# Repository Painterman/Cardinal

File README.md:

# Cardinal

 Introducing: Cardinal, a split, fully wireless, low profile with choc spacing and hotswap sockets with optional encoders, screens and 5 position switches.

 As this update this should be in a working state and mostly finished, you can find the Kicad project Gerbers ready to order, and the case files in /Case
 
# Why?

For a while now I have been using a ferris sweep on and off and wanted to go back to more keys and features. 
Looking at other keyboard projects i found about the Panasonic EVQWGD encoders and the 5 position switches like SKRHA line from alps and wanted to make a keyboard with both of these, options for displays and other features that I might like.

Fast-forward and here we are, my first keyboard design taking clues from multiple other community designs.

# Features

    -Fully wireless, designed around Nice!Nano or other controllers with the same pinout/wireless capability due to the lack of trss jack.
    -Reversible pcb.
    -2 encoders support per side, or 1 encoder and 1 5 position switch.
    -Choc spacing and hotswap sockets.
    -Oled display or Nice!View support.

 Things i might end up doing:
 
    - More versions: support for different encoders and for less keys.
    - Maybe a reduced choc spacing board.
    - Non hotswap version.
    - investigate into wireless charging

# BOM

Use this as a reference, you can find a more detailed build guide on the wiki.

| Part      | Quantity | Notes| 
| :-------------- | :---: | :------ |
| PCB | 2 | Use your preferred pcb manufacturing service, mine came from pcbgogo (not affiliated), the size of the pcbs is 135x100, so its a bit more expensive than the sub 100x100 |
| Pro Micro footprint microcontroller | 2 | Designed with Nice!Nano Bluetooth in mind, I’m using ProMicro NRF52840 |
| Choc key switches | 42 or less | You have the option to breakaway the extra pinkie column, or even just use less thumb keys |
| Choc hotswap sockets | Same as switches | 1 per key|
| 1N4148WS SOD123 diodes  | 48 or less | 1 per key, 2 per half for encoders and 2 for 5 way switch | 
| EVQWGD001 rotary encoders | 4 or less | I’m using only 2, but the board supports up to 4(2 per side)|
| 5-way switches SKRHA family   | 2 | SKRHADE010 are rated for more uses, I’m using SKRHABE010, rated for 1/5 the cycles and less expensive, here is the dataset : [SKRHA](https://www.mouser.es/datasheet/2/15/SKRH-1370966.pdf)|
| On/Off switch MSK-12C02 | 1 | Off to the right, on to the left, same on both halves |
| Lipo battery’s | 2 | You can use any you want, i like the 301230 size so it fits under the Pro Micro, but a bigger battery and a case it’s also a great option |
| Battery connectors | 2 | (optional) You can use any connector you like/have as long as the pitch its 1,5 mm, I’m using JST ZH|
| Reset switch | 2 | (optional) B3U-1000P|
| Keycaps | Same as switches | I like chosfox CFX and MBK, using CFX atm |
| 5-way switch keycap | 2 | I’m using ones that I don’t like until I design something better |
| Case | 2 | 3d printed case |

Most parts can be found on aliexpress easily, and I have seem a few offers to manufacture pcbs from vendors there, I have not tried any. My pcbs were ordered from [PCBgogo](https://www.pcbgogo.com/) and so far I’m happy with the cuality of the service and pcbs, im not affiliated with then but for now I can recommend then. Other popular option for manufacturing on the cheap is [JLCPCB](https://jlcpcb.com/) and can also recommend then, probably a better option overall due to shipping and EU import duties, prices were similar.

In terms of tenting options, the pcbs have 2 holes to support [Tenting Puck](https://splitkb.com/products/tenting-puck), i have not tested then as i don´t have any, but should fit. You could go with a case and cheap magnetic ring.

# Case

I have designed a simple case to use with the keyboard and to have a flat bottom so I can stick some kind of tenting option, I now use small kickstands for laptops.

The case design is really basic and also used it to try different cad programs so I can break free from fusion360 or other alternatives that are mostly online. Unfortunately, I will say that fusion and on shape are still the best options by a long shot for designing functional parts and Freecad/Ondsel are way too restrictive/hard to use. Even so I did end up using Ondsel to make the designs and on the /Case folder you can find stls for a 42 and 36 key configurations as well as svgs with the board outline, dxf to import into cad programs and my full Freecad project in case you wish to edit or modify then.

For printing the case, use any matterial you like and least 2 outer walls, so they end up solid, should print fine in all printers.

# Firmware

As this is a fully wireless build and intended to be used with [nice!nanos](), this board is intended to be used with [zmk]().
You can check my [main configuration](https://github.com/Painterman/zmk-config-cardinal) of the keyboard and in case you want to build your own firmware you could clone my main or use the [zmk module](https://github.com/Painterman/zmk-keyboard-cardinal) provided.
Both cases are [zmk studio](https://zmk.dev/docs/features/studio) and [keymap editor](https://github.com/nickcoutsos/keymap-editor) ready, for ease of use.

# Bling

Some photos, you can find more in the Pictures folder

# Inspirations and acknowledgments

First thanks to that weird friend with his weird keyboards

Heavy inspiration from Sweep https://github.com/davidphilipbarr/Sweep taking the overall shape and column stagger from it, as the reversible pcb design.

Extra pinkie column like corne https://github.com/foostan/crkbd as well as hotswap.

Inspiration from Hillside https://github.com/mmccoyd/hillside as its close to what I wanted, but also an encouragement to go further.

Encoder from Rollow  https://www.barbellboards.com/product/rollow as I fell in love with it.

5 position switches from Fulcrum https://github.com/dschil138/Fulcrum but with more keys.

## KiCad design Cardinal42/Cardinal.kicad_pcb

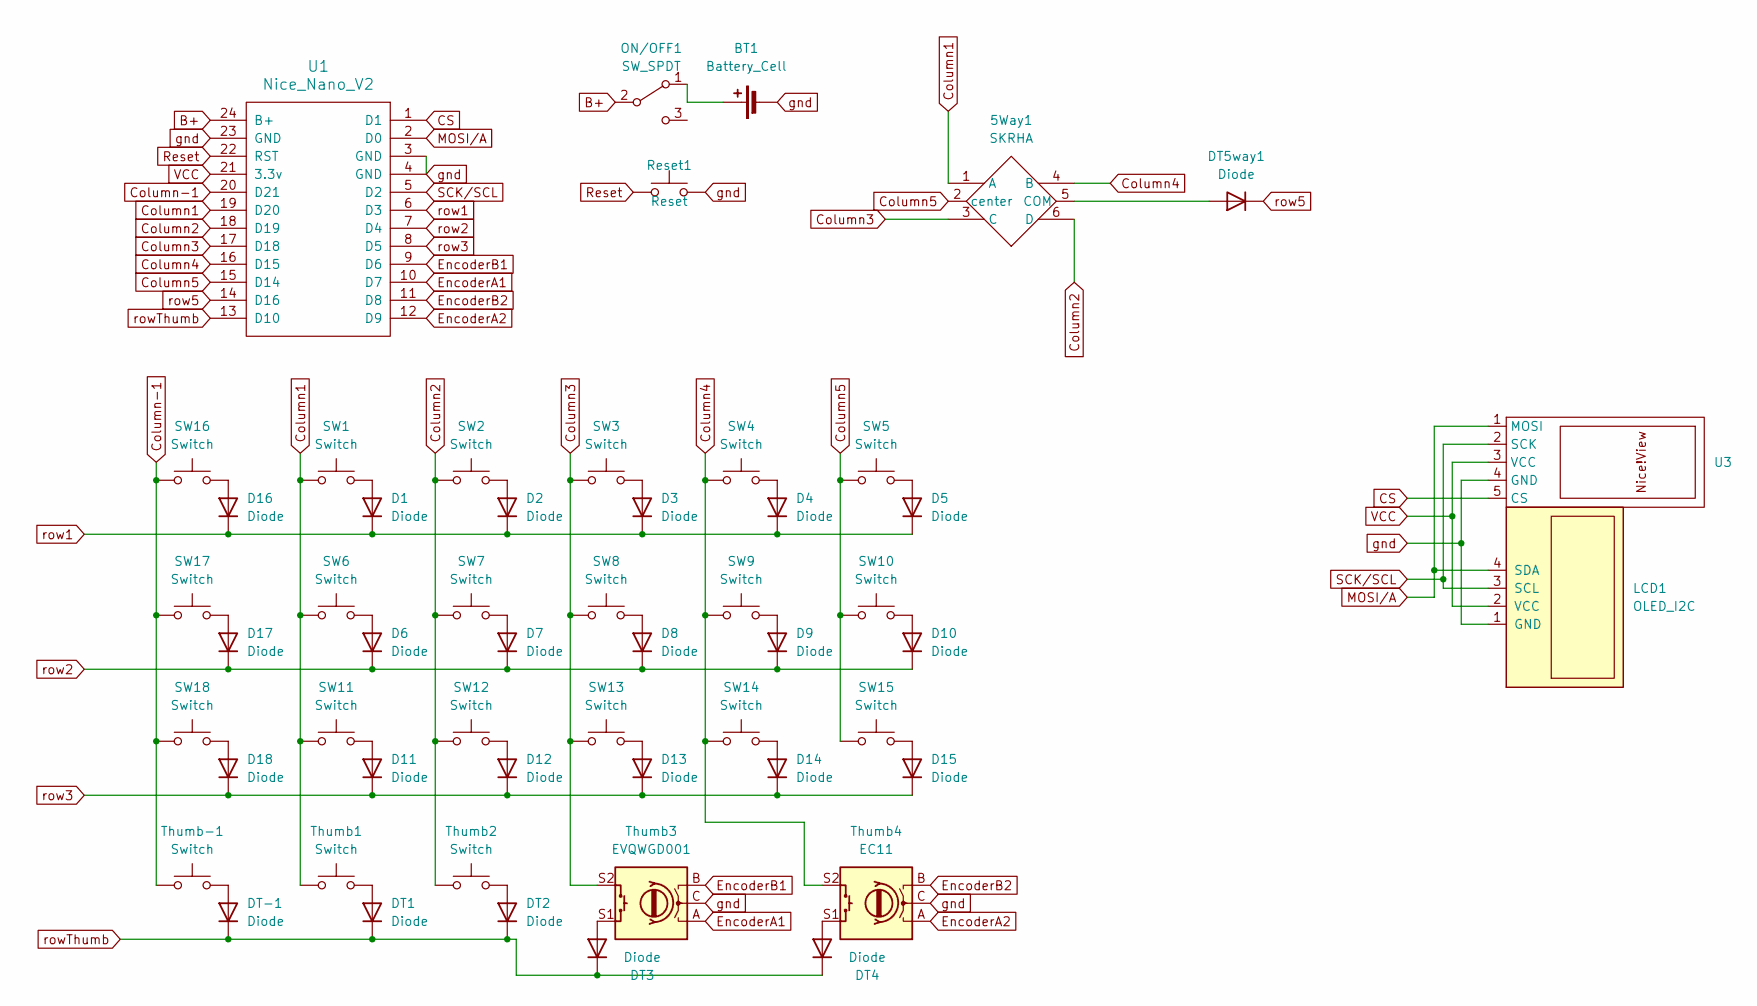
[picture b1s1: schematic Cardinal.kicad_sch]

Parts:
5Way1: SKRHA; SKRHA-boss_mod_doble
BT1: Battery_Cell; JST_ZH_2PIN_1.5MM
D1, D2, D3, D4, D5, D6, D7, D8, D9, D10, D11, D12, D13, D14, D15, D16, D17, D18: Diode; Diode_SOD-123_mod
DT1, DT2, DT3, DT4, DT5way1: Diode; Diode_SOD-123_mod
DT-1: Diode; Diode_SOD-123_mod
LCD1: OLED_I2C; OLED_I2C_128x32+NiceView
ON/OFF1: SW_SPDT; switch-MSK-12C02-smd
Reset1: Reset; SW_SPST_B3U-1000P_mod
SW1, SW2, SW3, SW4, SW5, SW6, SW7, SW8, SW9, SW10, SW11, SW12, SW13, SW14, SW15, SW16, SW17, SW18: Switch; Hotswap_Choc_V1_1.00u_mod
Thumb1, Thumb2: Switch; Hotswap_Choc_V1_1.00u_mod
Thumb3: EVQWGD001; RollerEncoder_Panasonic_EVQWGD001_mod
Thumb4: EC11; RollerEncoder_Panasonic_EVQWGD001_mod
Thumb-1: Switch; Hotswap_Choc_V1_1.00u_mod
U1: Nice_Nano_V2; ProMicro_jumpers
U3: (no value)

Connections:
B+: ON/OFF1.2 (B), U1.24 (B+)
CS: U1.1 (D1), U3.5 (CS)
Column1: 5Way1.1 (A), SW1.1, SW6.1, SW11.1, Thumb1.1, U1.19 (D20); also elsewhere on the board
Column2: 5Way1.6 (D), SW2.1, SW7.1, SW12.1, Thumb2.1, U1.18 (D19); also elsewhere on the board
Column3: 5Way1.3 (C), SW3.1, SW8.1, SW13.1, Thumb3.S2, U1.17 (D18); also elsewhere on the board
Column4: 5Way1.4 (B), SW4.1, SW9.1, SW14.1, Thumb4.S2, U1.16 (D15); also elsewhere on the board
Column5: 5Way1.2 (center), SW5.1, SW10.1, SW15.1, U1.15 (D14); also elsewhere on the board
Column-1: SW16.1, SW17.1, SW18.1, Thumb-1.1, U1.20 (D21)
EncoderA1: Thumb3.A, U1.10 (D7)
EncoderA2: Thumb4.A, U1.12 (D9)
EncoderB1: Thumb3.B, U1.9 (D6)
EncoderB2: Thumb4.B, U1.11 (D8)
MOSI/A: LCD1.4 (SDA), U1.2 (D0), U3.1 (MOSI)
unnamed 13: 5Way1.5 (COM), DT5way1.2 (A); also elsewhere on the board
unnamed 14: BT1.1 (+), ON/OFF1.1 (A); also elsewhere on the board
unnamed: D1.2 (A), SW1.2
unnamed: D2.2 (A), SW2.2
unnamed: D3.2 (A), SW3.2
unnamed: D4.2 (A), SW4.2
unnamed: D5.2 (A), SW5.2
unnamed: D6.2 (A), SW6.2
unnamed: D7.2 (A), SW7.2
unnamed: D8.2 (A), SW8.2
unnamed: D9.2 (A), SW9.2
unnamed: D10.2 (A), SW10.2
unnamed: D11.2 (A), SW11.2
unnamed: D12.2 (A), SW12.2
unnamed: D13.2 (A), SW13.2
unnamed: D14.2 (A), SW14.2
unnamed: D15.2 (A), SW15.2
unnamed: D16.2 (A), SW16.2
unnamed: D17.2 (A), SW17.2
unnamed: D18.2 (A), SW18.2
unnamed: DT1.2 (A), Thumb1.2
unnamed: DT2.2 (A), Thumb2.2
unnamed: DT3.2 (A), Thumb3.S1
unnamed: DT4.2 (A), Thumb4.S1
unnamed: DT-1.2 (A), Thumb-1.2
Reset: Reset1.1, U1.22 (RST)
SCK/SCL: LCD1.3 (SCL), U1.5 (D2), U3.2 (SCK)
VCC: LCD1.2 (VCC), U1.21 (3.3v), U3.3 (VCC)
gnd: BT1.2 (-), LCD1.1 (GND), Reset1.2, Thumb3.C, Thumb4.C, U1.3 (GND), U1.4 (GND), U1.23 (GND), U3.4 (GND); also elsewhere on the board
row1: D1.1 (K), D2.1 (K), D3.1 (K), D4.1 (K), D5.1 (K), D16.1 (K), U1.6 (D3)
row2: D6.1 (K), D7.1 (K), D8.1 (K), D9.1 (K), D10.1 (K), D17.1 (K), U1.7 (D4)
row3: D11.1 (K), D12.1 (K), D13.1 (K), D14.1 (K), D15.1 (K), D18.1 (K), U1.8 (D5)
row5: DT5way1.1 (K), U1.14 (D16)
rowThumb: DT1.1 (K), DT2.1 (K), DT3.1 (K), DT4.1 (K), DT-1.1 (K), U1.13 (D10)

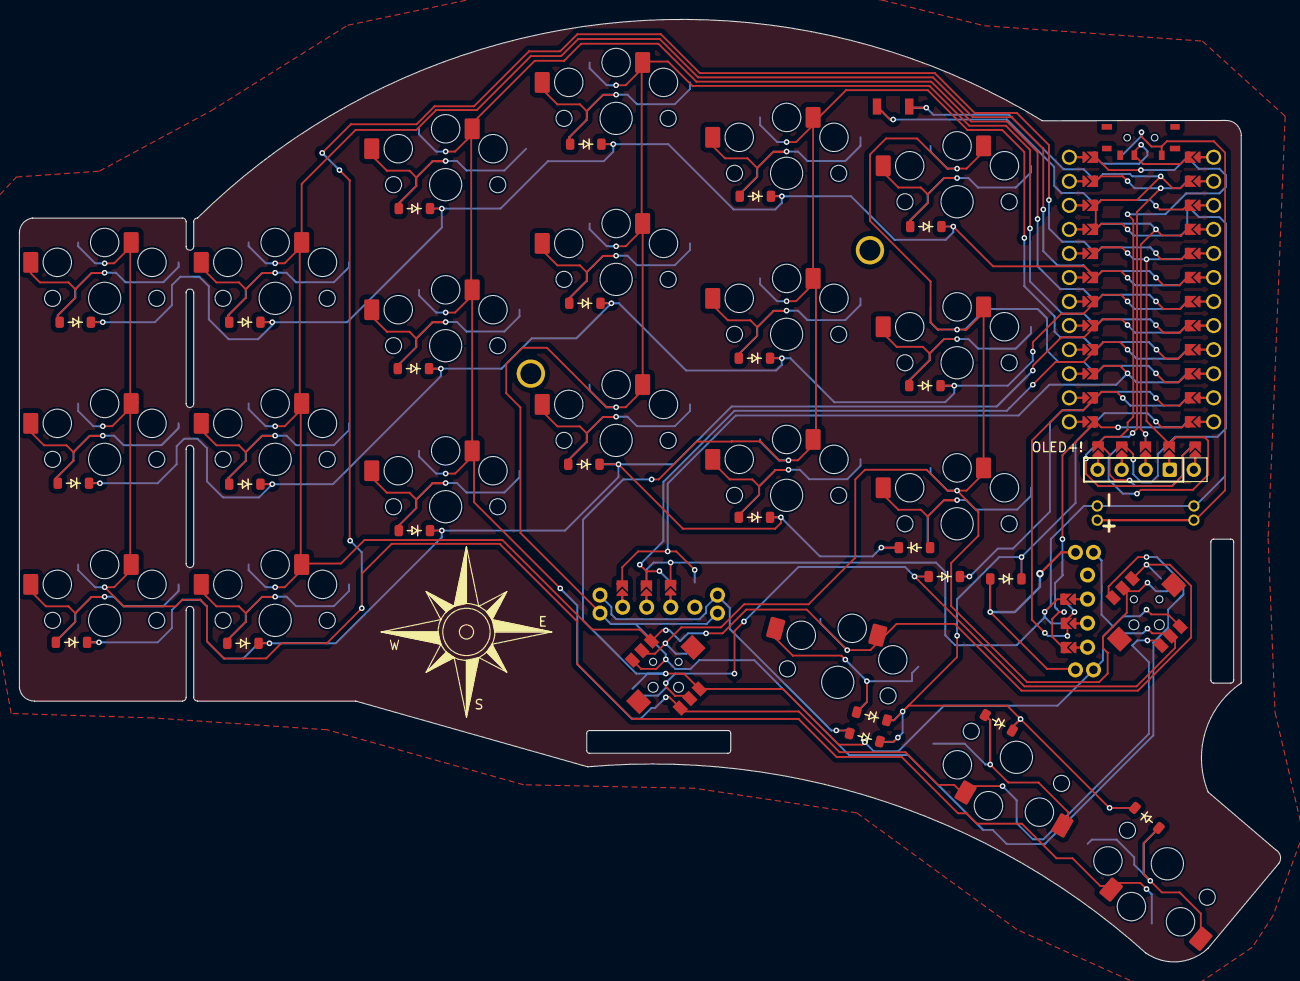
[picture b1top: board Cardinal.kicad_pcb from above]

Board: 2 copper layers, 133.2 x 99.5 mm, 55 parts (1 on the bottom side), 43 nets.

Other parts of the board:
5Way1#2: SKRHA; SKRHA-boss_mod_doble
BT1#2: Battery_Cell; JST_ZH_2PIN_1.5MM
OLED+!: OLED_I2C; OLED_I2C_128x32+NiceView

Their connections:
Column1: 5Way1#2.1 (A); also elsewhere on the board
Column2: 5Way1#2.6 (D); also elsewhere on the board
Column3: 5Way1#2.3 (C); also elsewhere on the board
Column4: 5Way1#2.4 (B); also elsewhere on the board
Column5: 5Way1#2.2 (center); also elsewhere on the board
unnamed 13: 5Way1#2.5 (COM); also elsewhere on the board
unnamed 14: BT1#2.1 (+); also elsewhere on the board
gnd: BT1#2.2 (-); also elsewhere on the board

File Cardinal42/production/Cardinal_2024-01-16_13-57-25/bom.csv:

Designator,Footprint,Quantity,Value,LCSC Part #
"_13, _12, _11, _10, _9, _8, _7, _6, _5, _4, _3, _2, ",37a111ce-96c9-42a8-b0d1-cee97aba29f6,13,,
"5Way1_2, 5Way1",SKRHA-boss_mod_doble,2,SKRHA,
"BT1_2, BT1",JST_ZH_2PIN_1.5MM,2,Battery_Cell,
"D1, D10, D11, D12, D13, D14, D15, D16, D17, D18, D2, D3, D4, D5, D6, D7, D8, D9, DT-1, DT1, DT2, DT3, DT4, DT5way1",Diode_SOD-123_mod,24,Diode,
OLED+!,OLED_I2C_128x32+NiceView,1,OLED_I2C,
ON/OFF1,switch-MSK-12C02-smd,1,SW_SPDT,
Reset1,SW_SPST_B3U-1000P_mod,1,Reset,
"SW1, SW10, SW11, SW12, SW13, SW14, SW15, SW16, SW17, SW18, SW2, SW3, SW4, SW5, SW6, SW7, SW8, SW9, Thumb-1, Thumb1, Thumb2",Hotswap_Choc_V1_1.00u_mod,21,Switch,
Thumb3,RollerEncoder_Panasonic_EVQWGD001_mod,1,EVQWGD001,
Thumb4,RollerEncoder_Panasonic_EVQWGD001_mod,1,EC11,
U1,ProMicro_jumpers,1,Nice_Nano_V2,

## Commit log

2023-12-07 First commit
    Initialization of the proyect, pending of refining the PCB and generating gerbers
2023-12-08 Flip FIx
    Fixed a lot of footprints and traces that were "upside down", my fault when i initially made the jump-pads.
    Prep work done for column -1 being detachable.
    Testing fill plane, no gnd/vcc for it, shouldnt be necessary.
    Still planing silkscreen.
2024-01-15 Release: V0.9
    Final desing mostly done, maybe one or two things left to refine.
    Added cutouts to reduce number of keys.
    Added logo.
    Added support for tenting puck, only 2 screws and maybe removed latter.
    Tweaked traces.
    Tested for plated holes, not convinced enough, changing in future version should be easy, but could make manufacturing problems due to the spacing from holes to pads.
2024-01-16 Minor update
    Minor update to footprints/size
2024-01-31 Update PCB V0.99
    After ordering pcbs and while testing then i noticed one of the pads its not conected, fixed now, at least its from one of the switches and i can add a jumper to it
2024-02-14 Probably V1
    Most likely this will be the release 1.0 for now on, after fixing 2 wrong traces in the desing, luckily things were an easy fix cutting a trace and adding a wire
2024-02-14 Added more imgs
2024-04-17 Big update
    Double checked most things to make sure they are fine.
    Update to readme with case information.
    Case files and extras.
    Grammar check.
    Mostly done again :D.
2024-06-27 Update README.md
    Changed the recomended 5 way switch
2024-06-27 Knob files
    Update to the knob files to make then available, just a start on then, still need more refinement
2025-09-24 Add module info
    Added information about zmk module and firmware.
